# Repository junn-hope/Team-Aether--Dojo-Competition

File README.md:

# Team-Aether--Dojo-Competition

This is a reposritory for all things Dojo Competition with regards to our team.

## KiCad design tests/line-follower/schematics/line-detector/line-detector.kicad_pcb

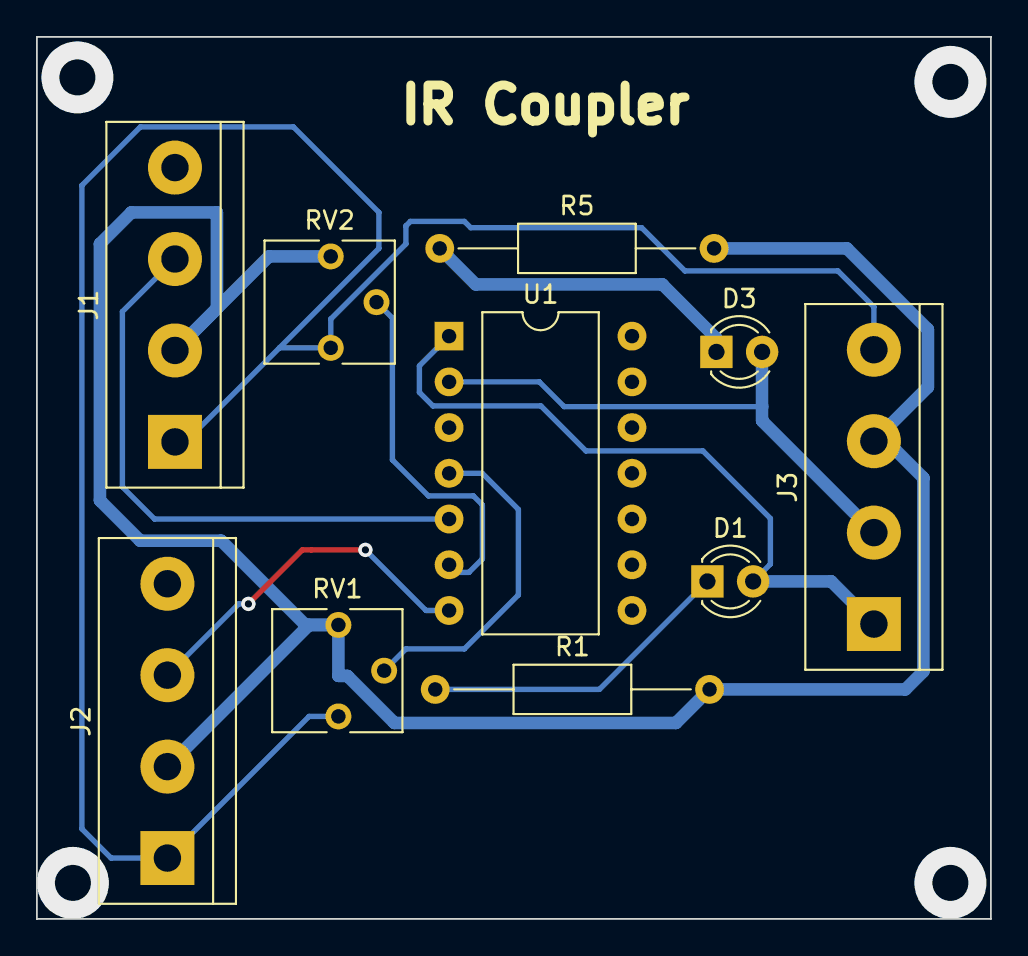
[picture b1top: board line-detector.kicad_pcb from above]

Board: 2 copper layers, 53.0 x 49.0 mm, 10 parts (0 on the bottom side), 10 nets.

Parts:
D1, D3: LED; LED_D3.0mm
J1: ir_module1; TerminalBlock_bornier-4_P5.08mm
J2: ir_module2; TerminalBlock_bornier-4_P5.08mm
J3: ouput_to_mcu; TerminalBlock_bornier-4_P5.08mm
R1, R5: 220R; R_Axial_DIN0207_L6.3mm_D2.5mm_P15.24mm_Horizontal
RV1, RV2: 10k; Potentiometer_Vishay_T73YP_Vertical
U1: LM339; DIP-14_W10.16mm

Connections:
GND: J1.2, J2.2, J3.3, R1.2, R5.2, RV1.3, RV2.3
IN1: J1.3, U1.5 (+)
IN2: J2.3, U1.7 (+)
unnamed: D1.1 (K), R1.1
unnamed: D3.1 (K), R5.1
unnamed: RV1.2, U1.4 (-)
unnamed: RV2.2, U1.6 (-)
OUT1: D3.2 (A), J3.2, U1.2
OUT2: D1.2 (A), J3.1, U1.1
VCC: J1.1, J2.1, J3.4, RV1.1, RV2.1

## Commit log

2022-08-22 created: schematics for IR modules
2022-08-25 added: arduino code for line follower
2022-09-15 added ir couplet
